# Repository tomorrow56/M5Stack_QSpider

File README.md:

# M5Stack_QSpider

## Quadruped Spider Robot for M5Stack
It is a quadruped walking robot using M5Stack and nine toy servos (SG90). It utilizes a custom servo module board for M5Stack equipped with PCA9685.

M5Stackとトイサーボ(SG90)x9個を使用した四脚歩行ロボットです。PCA9685を搭載したM5Stack用の自作サーボモジュール基板を使用しています。

Botttom View

### 3D Print Data

The 3D print data is available below. Please print four sets of parts from the 'leg' folder, as each set corresponds to one leg.

3Dプリント用のデータは以下にあります。legフォルダ以下の部品は1本分なので4個印刷してください。

[3D Print Data](3dprint/leg/)

The fully assembled main body and each leg (two types, diagonal combinations) is uploaded in STEP format. Please refer to them during assembly.

組立済の本体全体・各脚(対角の組合せで2種類)はSTEP形式でアップロードしてありますので、参考にしてください。

[STEP Data](3dprint/)

### M5Stack Servo Driver Module
### M5Stack用サーボモジュール基板
The circuit diagram, Gerber data, and KiCad design files have been published in this repository under the `pcb/` folder.

回路図、ガーバーデータ、KiCadの設計データは本リポジトリの `pcb/` フォルダ以下で公開しています。

[PCB Design Data](pcb/M5_PCA9685_v03/)

Production outputs (Gerber, BOM, pick-and-place) are available in `pcb/production/`.

[Production Data](pcb/production/)

生産用データ（ガーバーやBOM、実装座標）も `pcb/production/` に用意しています。

[生産用データ](pcb/production/)

### Parts needed (excluding 3D print parts)
* M5Stack Basic x 1
* [SG-90](https://akizukidenshi.com/catalog/g/gM-08761/) X 9
* [M5Stack Servo Driver Module](pcb/M5_PCA9685_v03/) (PCA9685 based servo controller board) x 1
  * Please refer to `pcb/production` for implementation data.
* [Battery Holder for 4x AA](https://akizukidenshi.com/catalog/g/gP-03087/) (For servo power)
* [Pololu S9V11F5](https://www.pololu.com/product/2865) (Step-up/step-down voltage regulator, generates 5V for M5Stack from AA battery)
  * [Switch-Sciense S9V11F5](https://www.switch-science.com/products/3246)
* M2x8mm Tapping Screws (Approximately 40)
* [Wiring Lead, Red/Black](https://akizukidenshi.com/catalog/g/g131311/)
* [Connector Housing 2P](https://akizukidenshi.com/catalog/g/g112151/)
* [Double-sided Adhesive Gel Tape](https://jp.daisonet.com/products/4550480578279) (For fixing servo bottom_Spacer)

### 必要な部品 (3Dプリント部品以外)
* M5Stack Basic x 1
* [SG-90](https://akizukidenshi.com/catalog/g/gM-08761/) X 9
* [M5Stack用サーボモジュール基板](pcb/M5_PCA9685_v03/) (PCA9685搭載サーボコントローラ基板) x 1
  * 実装は `pcb/production` の内容を参考にしてください
* [電池ボックス単4×4本](https://akizukidenshi.com/catalog/g/gP-03087/) (サーボ電源用)
* [Pololu S9V11F5](https://www.pololu.com/product/2865) (昇降圧型電圧レギュレータ、単4電池からM5Stack用5Vを生成)
  * [Switch-Sciense S9V11F5](https://www.switch-science.com/products/3246)
* M2x8mmのタッピングビス(約40本)
* [配線用リード線 赤・黒](https://akizukidenshi.com/catalog/g/g131311/)
* [コネクター用ハウジング 2P](https://akizukidenshi.com/catalog/g/g112151/)
* [両面粘着ゲルテープ](https://jp.daisonet.com/products/4550480578279) (サーボ bottom_Spacer 固定用)

## ソフトウエア: Software
There are sketches for ArduinoIDE in the 'examples' folder. There are two types available for web interface and ESP-NOW.

ArduinoIDE用のスケッチがexample以下にあります。Webインターフェース用とESP-NOW用の2種類があります。

### Controler with Web Interface Webインターフェース
It starts as a WiFi access point and can be controlled from a web browser.

WiFiのアクセスポイントとして起動し、Webブラウザからコントロールできます。

### Controller for ESP-NOW mode ESP-NOW用コントローラ
The source code for the ESP-NOW controller is available below. Here, a modified Famicom controller is used.

ESP-NOW用コントローラのソースコードは以下にあります。ここではファミコン用コントローラを改造して使用しています。

<https://github.com/tomorrow56/nespad-arduino>

### Protopedia
<https://protopedia.net/prototype/2464>

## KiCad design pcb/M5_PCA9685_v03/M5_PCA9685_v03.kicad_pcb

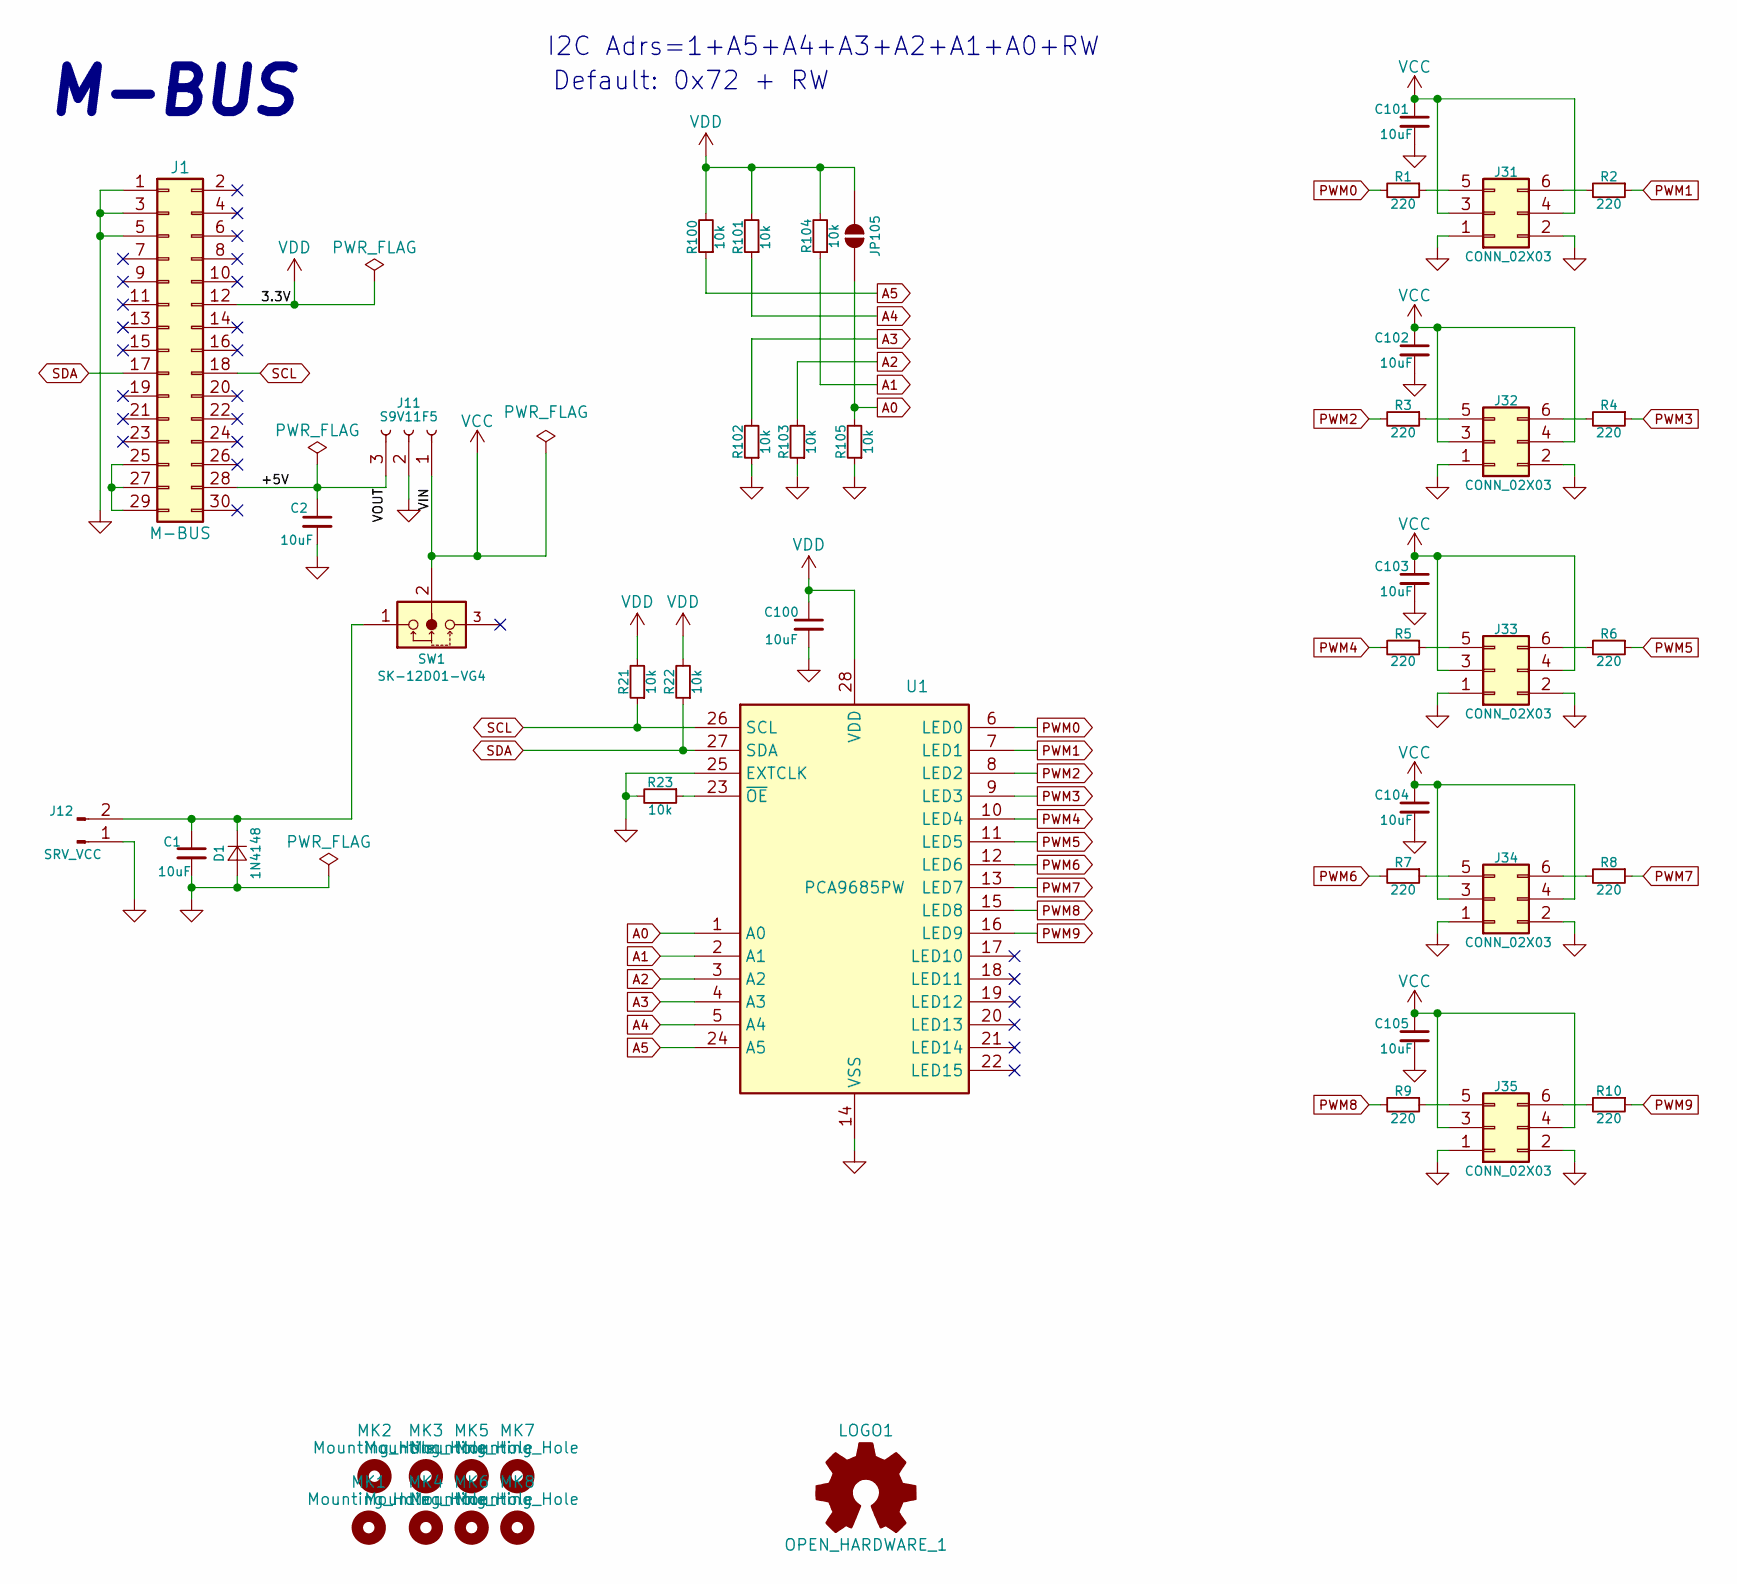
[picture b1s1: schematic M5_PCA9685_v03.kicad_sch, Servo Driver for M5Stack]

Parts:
C1, C2, C100, C101, C102, C103, C104, C105: 10uF; C_0603_1608Metric
D1: 1N4148; D_SOD-323
J1: M-BUS; Pin_Header_MBUS_SMD_TH
J11: S9V11F5; PinSocket_1x03_P2.54mm_Vertical
J12: SRV_VCC; PinHeader_1x02_P2.54mm_Vertical
J31, J32, J33, J34, J35: CONN_02X03; PinHeader_2x03_P2.54mm_Vertical
JP105: SOLDERJUMPER; SolderJumper-2_P1.3mm_Open_RoundedPad1.0x1.5mm
LOGO1: OPEN_HARDWARE_1; OSHW-logo_silkscreen-front_3mm
MK1, MK2, MK3, MK4: Mounting_Hole; MountingHole_3.2mm_M3
MK5, MK6, MK7, MK8: Mounting_Hole; MountingHole_2.2mm_M2
R1, R2, R3, R4, R5, R6, R7, R8, R9, R10: 220; R_0603_1608Metric
R21, R22, R23, R100, R101, R102, R103, R104, R105: 10k; R_0603_1608Metric
SW1: SK-12D01-VG4; slide_switch_angled
U1: PCA9685PW; TSSOP-28_4.4x9.7mm_P0.65mm

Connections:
/+5V: C2.1, J1.28, J11.3
A0: JP105.2 (B), R105.2, U1.1 (A0)
A1: R104.1, U1.2 (A1)
A2: R103.2, U1.3 (A2)
A3: R102.2, U1.4 (A3)
A4: R101.1, U1.5 (A4)
A5: R100.1, U1.24 (A5)
GND: C1.2, C2.2, C100.2, C101.2, C102.2, C103.2, C104.2, C105.2, D1.2 (A), J1.1, J1.3, J1.5, J11.2, J12.1, J31.1, J31.2, J32.1, J32.2, J33.1, J33.2, J34.1, J34.2, J35.1, J35.2, R23.2, R102.1, R103.1, R105.1, U1.14 (VSS), U1.25 (EXTCLK)
unnamed: C1.1, D1.1 (K), J12.2, SW1.1
unnamed: J1.25, J1.27, J1.29
unnamed: J31.5, R1.1
unnamed: J31.6, R2.2
unnamed: J32.5, R3.1
unnamed: J32.6, R4.2
unnamed: J33.5, R5.1
unnamed: J33.6, R6.2
unnamed: J34.5, R7.1
unnamed: J34.6, R8.2
unnamed: J35.5, R9.1
unnamed: J35.6, R10.2
unnamed: R23.1, U1.23 (~OE)
PWM0: R1.2, U1.6 (LED0)
PWM1: R2.1, U1.7 (LED1)
PWM2: R3.2, U1.8 (LED2)
PWM3: R4.1, U1.9 (LED3)
PWM4: R5.2, U1.10 (LED4)
PWM5: R6.1, U1.11 (LED5)
PWM6: R7.2, U1.12 (LED6)
PWM7: R8.1, U1.13 (LED7)
PWM8: R9.2, U1.15 (LED8)
PWM9: R10.1, U1.16 (LED9)
SCL: J1.18, R21.1, U1.26 (SCL)
SDA: J1.17, R22.1, U1.27 (SDA)
VCC: C101.1, C102.1, C103.1, C104.1, C105.1, J11.1, J31.3, J31.4, J32.3, J32.4, J33.3, J33.4, J34.3, J34.4, J35.3, J35.4, SW1.2
VDD: C100.1, J1.12, JP105.1 (A), R21.2, R22.2, R100.2, R101.2, R104.2, U1.28 (VDD)

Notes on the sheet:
I2C Adrs=1+A5+A4+A3+A2+A1+A0+RW
M-BUS
Default: 0x72 + RW

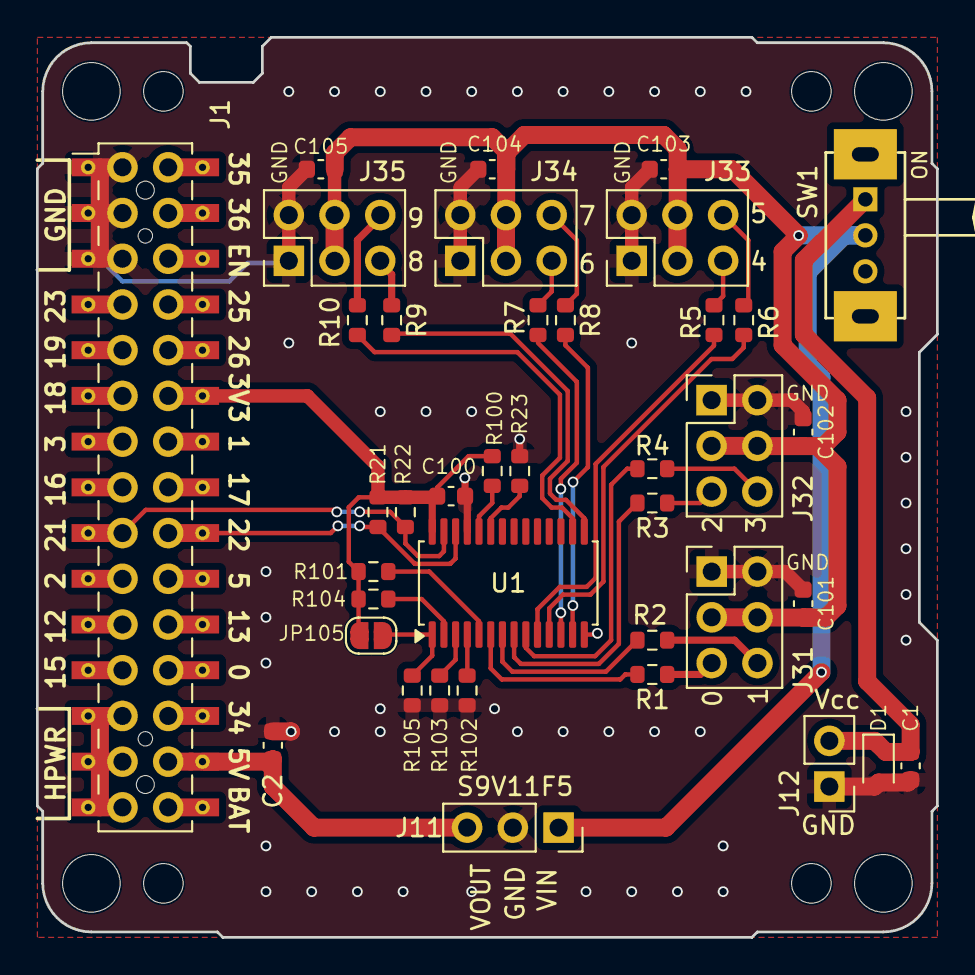
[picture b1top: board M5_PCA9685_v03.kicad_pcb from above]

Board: 2 copper layers, 50.0 x 50.0 mm, 48 parts (1 on the bottom side), 35 nets.

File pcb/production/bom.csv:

Designator,Footprint,Quantity,Value,LCSC Part #
"C1, C100, C101, C102, C103, C104, C105, C2",0603,8,10uF,
D1,D_SOD-323,1,1N4148,
J1,Pin_Header_MBUS_SMD_TH,1,M-BUS,
J11,PinSocket_1x03_P2.54mm_Vertical,1,S9V11F5,
J12,PinHeader_1x02_P2.54mm_Vertical,1,SRV_VCC,
"J31, J32, J33, J34, J35",PinHeader_2x03_P2.54mm_Vertical,5,CONN_02X03,
LOGO1,OSHW-logo_silkscreen-front_3mm,1,OPEN_HARDWARE_1,
"MK1, MK2, MK3, MK4",MountingHole_3.2mm_M3,4,Mounting_Hole,
"MK5, MK6, MK7, MK8",MountingHole_2.2mm_M2,4,Mounting_Hole,
"R1, R10, R2, R3, R4, R5, R6, R7, R8, R9",0603,10,220,
"R100, R101, R102, R103, R104, R105, R21, R22, R23",0603,9,10k,
SW1,slide_switch_angled,1,SK-12D01-VG4,
U1,TSSOP-28_4.4x9.7mm_P0.65mm,1,PCA9685PW,

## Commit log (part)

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2021-09-10 Add example of multitask version
    Multitasking version of web control and avatar display. Changed the expression a little.
2024-01-03 replaced all stl data
